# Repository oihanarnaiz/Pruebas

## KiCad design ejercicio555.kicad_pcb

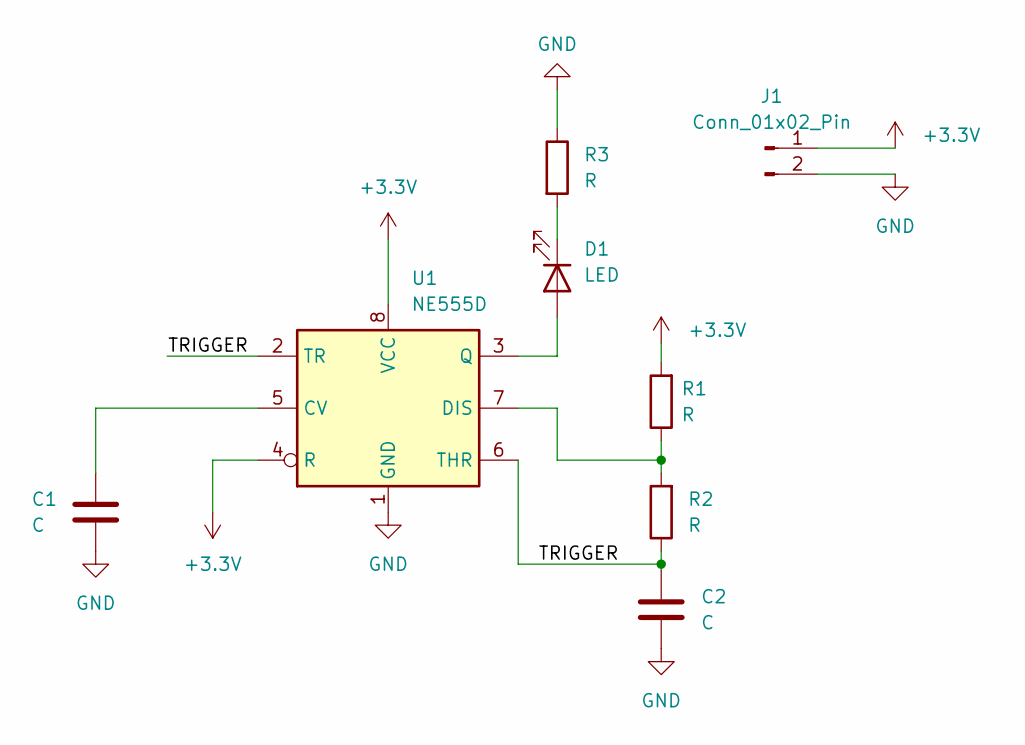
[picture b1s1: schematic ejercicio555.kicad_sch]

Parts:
C1, C2: C; C_0603_1608Metric
D1: LED; LED_1812_4532Metric
J1: Conn_01x02_Pin; JWT_A3963_1x02_P3.96mm_Vertical
R1, R2, R3: R; R_0603_1608Metric
U1: NE555D; SOIC-8_3.9x4.9mm_P1.27mm

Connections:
+3.3V: J1.1, R1.2, U1.4 (R), U1.8 (VCC)
/TRIGGER: C2.1, R2.1, U1.2 (TR), U1.6 (THR)
GND: C1.2, C2.2, J1.2, R3.1, U1.1 (GND)
unnamed: D1.2 (A), U1.3 (Q)
unnamed: D1.1 (K), R3.2
unnamed: C1.1, U1.5 (CV)
unnamed: R1.1, R2.2, U1.7 (DIS)

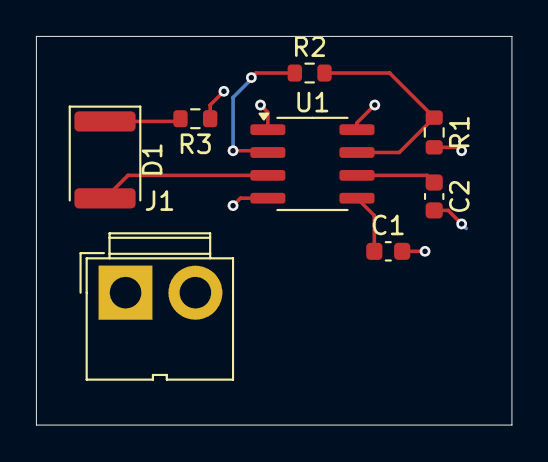
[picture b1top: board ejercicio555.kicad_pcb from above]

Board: 4 copper layers, 26.4 x 21.6 mm, 8 parts (0 on the bottom side), 7 nets.

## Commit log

2024-09-22 Añadido primer diseño de un 555 en kiCad
